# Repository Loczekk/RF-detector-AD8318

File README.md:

# RF-detector-AD8318

## Photos

## Initial Measurements 
soon

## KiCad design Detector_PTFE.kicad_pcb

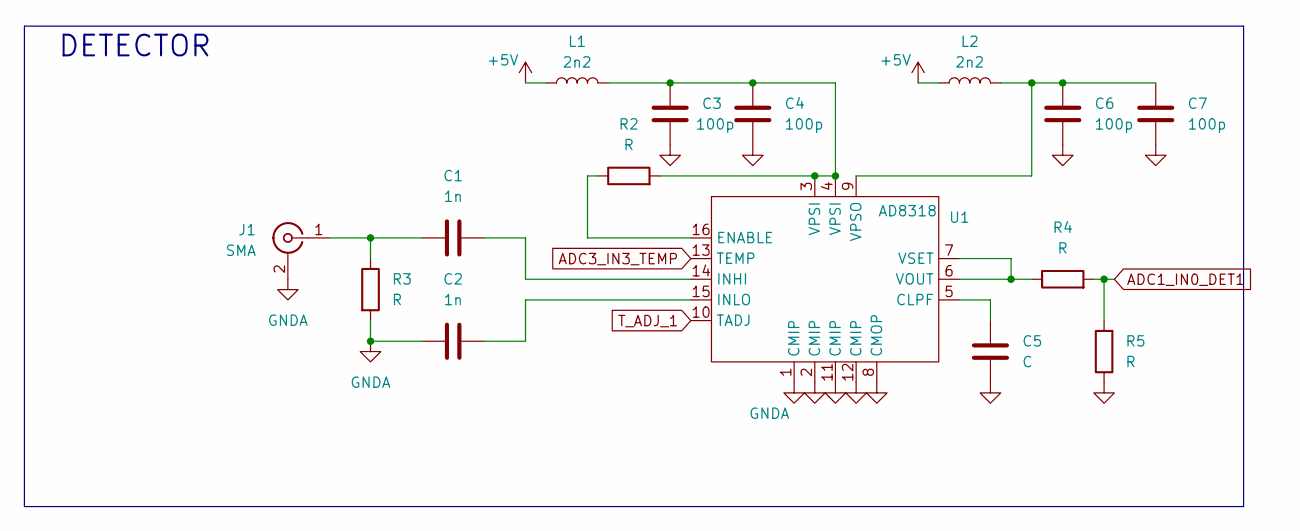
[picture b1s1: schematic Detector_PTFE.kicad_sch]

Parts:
C1, C2: 1n; C_0603_1608Metric
C3, C4, C6, C7: 100p; C_0402_1005Metric
C5: C; C_0402_1005Metric
J1: SMA; SMA_Amphenol_132289_EdgeMount
L1, L2: 2n2; L_0603_1608Metric
R2, R3, R4, R5: R; R_0402_1005Metric
U1: AD8318; LGA-16_4x4mm_P0.65mm_LayoutBorder4x4y

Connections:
+5V: L1.1, L2.1
ADC1_IN0_DET1: R4.2, R5.2
ADC3_IN3_TEMP: U1.13 (TEMP)
GNDA: C2.1, C3.1, C4.1, C5.1, C6.1, C7.1, J1.2 (Ext), R3.2, R5.1, U1.1 (CMIP), U1.2 (CMIP), U1.8 (CMOP), U1.11 (CMIP), U1.12 (CMIP)
unnamed: C3.2, C4.2, L1.2, R2.2, U1.3 (VPSI), U1.4 (VPSI)
unnamed: C1.1, J1.1 (In), R3.1
unnamed: C5.2, U1.5 (CLPF)
unnamed: R2.1, U1.16 (ENABLE)
unnamed: C1.2, U1.14 (INHI)
unnamed: C2.2, U1.15 (INLO)
unnamed: R4.1, U1.6 (VOUT), U1.7 (VSET)
unnamed: C6.2, C7.2, L2.2, U1.9 (VPSO)
T_ADJ_1: U1.10 (TADJ)

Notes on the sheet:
DETECTOR

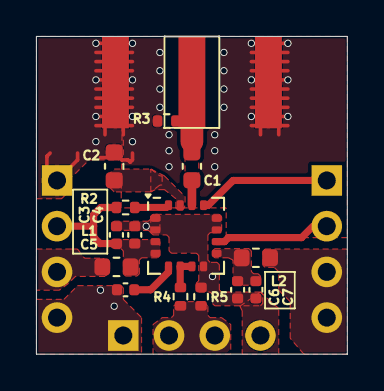
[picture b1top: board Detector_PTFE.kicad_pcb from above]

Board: 2 copper layers, 17.3 x 17.7 mm, 15 parts (0 on the bottom side), 11 nets.
